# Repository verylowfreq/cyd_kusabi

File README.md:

# CyberDeck — ESP32-S3 SSH 端末

ESP32-S3 で作る、日本語入力可能な SSH 端末です。USB キーボードで打ち、480x320 の SPI 液晶に VT 互換のターミナルを出します。Wi-Fi で SSH に入り、PC を開かずに作業できます。

想定している使い方:

- 手元の簡易な SSH 端末として
- SSH 先で動く AI エージェント（Claude Code / Codex CLI など）に指示を出す端末として
- マイコンならではの GPIO・I2C・UART を直接触れる端末として
- 日本語のテキストを書く道具として
- WebAssemblyでユーザーアプリを書いて、スタンドアロンの制御端末として

**A SSH terminal built on the ESP32-S3.** It connects to Wi-Fi, takes
input from a USB keyboard, and shows an 80x26 VT terminal on a
480x320 SPI LCD. You can log in to a remote host over SSH (PTY, public-key or
password auth) and copy files with `scp`, all without a PC. It also has
built-in SKK Japanese input, a text editor, a small shell with GPIO / I2C /
ADC / UART commands, microSD storage, and user apps written in WebAssembly
(C or Rust SDK). Firmware is ESP-IDF v5.5 in C11, and the KiCad data for the
motherboard is included. Documentation is mainly in Japanese.

## できること

- **SSH**（libssh2）: PTY 付きで `top` や全画面アプリが動く。公開鍵認証（実機で鍵を作る）と
  パスワード認証、`known_hosts` によるホスト鍵の確認、切れたときの自動再接続
- **`scp`**: この機械だけでファイルを送る・取る（Linux / Windows の OpenSSH 相手で確認）
- **ターミナル**: UTF-8・全角幅・SGR 色・スクロール領域など VT100/xterm の主要部分。
  スクロールバック 200 行
- **SKK 日本語入力**: SKK-JISYO.L（約 17.5 万語）をフラッシュに載せ、学習結果も残す
- **テキストエディタ**: `edit <file>` で microSD 上のファイルを日本語入力つきで編集
- **シェル**: 行編集つき。ファイル操作、`wget`（HTTP / HTTPS）、シリアル端末 `uart`、
  `gpio` / `adc` / `i2c` など
- **WebAssembly アプリ**: `wasm run` で microSD 上の `.wasm` を実行。
  ファームを焼き直さずに機能を足せる。SDK は C と Rust
  （コンソール・ファイル・GPIO・ADC・I2C・UART・TCP/UDP・TLS）
- **ステータス帯**: `set statusbar on`（再起動後）で、Wi-Fi・SSH・かな入力・SD・電池電圧などを
  画面下に出す（既定は出さない。出すと本文は 80 x 25）

使い方の詳細は [取扱説明書 (docs/MANUAL.md)](docs/MANUAL.md) にあります。

## ハードウェア

| | |
|---|---|
| MCU | ESP32-S3-WROOM-1-N16R8（16MB flash / 8MB octal PSRAM）。Freenove ESP32-S3 開発ボードをマザーボードに載せる |
| 表示 | 480x320 SPI 液晶（ILI9488）。東雲フォント 12px で 80 桁 x 26 行（2 倍表示で 40 x 13） |
| 入力 | USB キーボード（ESP32-S3 の USB-OTG をホストとして使用） |
| 記憶 | microSD |
| 外部端子 | D-sub 9 ピン（RS-232C）、Grove（GPIO / I2C / UART） |
| 電源 | 単3形 NiMH 電池 x2（本体では充電しない） |

マザーボードの KiCad データ（回路図・基板・プロジェクト内ライブラリ・JLCPCB 用ガーバー）は
[hardware/cdk_motherboard/](hardware/cdk_motherboard/) にあります。
ピン割り当てや設計判断は [HARDWARE_DESIGN.md](HARDWARE_DESIGN.md) を参照してください。

> **基板 v1 には既知の誤りがあります。** microSD の SPI 4 本（GPIO39〜42）は、回路図・基板データ上の
> 信号名が実物と違います。ファームウェアのピン指定（`cdk_board.h`）が正しい方です。
> 詳しくは [HARDWARE_DESIGN.md の「基板 v1 の既知の誤り」](HARDWARE_DESIGN.md#基板-v1-の既知の誤り) を見てください。

ファームウェアは試作機として使った **M5Stack CoreS3** 向けにもビルドできます
（`--board cores3`）。

## リポジトリの構成

```
cyberdeck_firmware/      ファームウェア（ESP-IDF プロジェクト）
  components/              ESP-IDF に依存しない純 C のコア（PC 上でもビルド・テストする）
  components_port/         ESP-IDF に依存する部分（表示・USB・SD・Wi-Fi・SSH など）
  main/                    起動とコマンド
  host/                    PC 上で回す単体テスト（ctest）
  tools/                   cdk.py（ビルド・書き込み・画面取得など）、フォント・辞書の変換
  wasm-sdk/                WebAssembly アプリの SDK（C / Rust）
  wasm-apps/               サンプルアプリ
  DESIGN.md                ファームウェアの設計書
hardware/cdk_motherboard/  マザーボードの KiCad データ
docs/MANUAL.md             取扱説明書
images/                    この README の写真と回路図
LICENSE                    MIT License
HARDWARE_DESIGN.md         ハードウェア仕様と検証の記録
ABOUT.md                   最初の企画（開発開始時の要求）
DEV_STATS.md               開発の統計
```

## ビルド

必要なもの:

- [ESP-IDF v5.5.5](https://docs.espressif.com/projects/esp-idf/en/v5.5.5/)
- PC 側のテストには clang、CMake、Ninja、Python 3
- `tools/cdk.py` は pyserial の入った Python で動かす（`export.ps1` の後の `python` でよい）
- `tools/gen_secrets.py` は git を使う（生成物が gitignore されているかを確かめるため）
- 開発は Windows（PowerShell）で行っています

### 1. 初回だけ: `secrets.h` を作る

ファームは `main/secrets.h` を読みます。これは Wi-Fi・SSH の初期値を入れるためのファイルで、
リポジトリには入っていません。リポジトリ直下に `.env` を作り、
`tools/gen_secrets.py` で生成してください。値は空のままでもかまいません
（起動後に `set wifi.ssid ...` などで設定でき、NVS に保存されます）。

```
TEST_WIFI_SSID=
TEST_WIFI_PSK=
TEST_SSHSERVER_HOST=
TEST_SSHSERVER_USERNAME=
TEST_SSHSERVER_PASSWORD=
```

```powershell
cd cyberdeck_firmware
python tools\gen_secrets.py
```

`.env` と `secrets.h` は gitignore 済みです。値をコミットしないでください。

### 2. ビルドと書き込み

```powershell
. <ESP-IDF のパス>\export.ps1
python tools\cdk.py build --board v1    # v1 = このリポジトリの基板。CoreS3 なら cores3
python tools\cdk.py flash
python tools\cdk.py selftest            # 起動 → 画面を取得して PC 側の基準画像と比較
```

`selftest` は PC 側で基準画像を描いて比べるので、先に下の「PC 上のテスト」で `build-host` を作っておいてください。
`--board` は最初の 1 回だけ付ければ、次からは省いても前回の基板を引き継ぎます。

v1 は書き込み・ログ用と制御用の 2 本のシリアルを使います。COM ポートの既定は開発機のもの
（v1: 書き込み・ログ COM76 / 制御 COM75）なので、違う場合は
`python tools\cdk.py --prog COM5 --log COM5 --ctrl COM6 flash` のようにサブコマンドの**前**に書くか、
環境変数 `CDK_PROG` / `CDK_LOG` / `CDK_CTRL` で指定します。
詳しくは [取扱説明書の 12 章](docs/MANUAL.md#12-ファームウェアを更新する) と
[cyberdeck_firmware/README.md](cyberdeck_firmware/README.md) を参照してください。

### SKK 辞書

辞書はリポジトリに含めていません。SKK-JISYO.L を取ってきて、別パーティションに書き込みます。

```powershell
curl -O https://skk-dev.github.io/dict/SKK-JISYO.L.unannotated.gz
# 展開してから
python tools\cdk.py dict SKK-JISYO.L.unannotated
```

### PC 上のテスト（実機不要）

```powershell
cd cyberdeck_firmware
cmake -S host -B build-host -G Ninja -DCMAKE_C_COMPILER=clang
cmake --build build-host
ctest --test-dir build-host --output-on-failure
```

VT パーサ、文字幅、フォント描画、SKK、シェル、WebAssembly の実行系などは
`components/` の純 C コードで、PC 上で検証できます。

## 開発について

このファームウェアは、AI エージェント（Claude Code）が実機でのビルド・書き込み・
画面の取得まで自分で回しながら開発しました。人間は方針の判断、配線や目視の確認などを
担当しています。その経過の数字（ビルド回数、不具合の数と見つけ方、人間が介入した回数など）を
[DEV_STATS.md](DEV_STATS.md) にまとめています。

設計の判断とその理由は [cyberdeck_firmware/DESIGN.md](cyberdeck_firmware/DESIGN.md) に残しています。

## ライセンス

[MIT License](LICENSE) © 2026 Mitsumine Suzu (verylowfreq)

同梱しているサードパーティのコードとデータは、それぞれのライセンスに従います。

| もの | 場所 | ライセンス |
|---|---|---|
| libssh2 1.11.1 | `cyberdeck_firmware/components_port/libssh2/upstream/` | BSD-3-Clause（`COPYING`） |
| wasm3（commit 2b4a5fa） | `cyberdeck_firmware/components_port/wasm3/upstream/` | MIT（`LICENSE`） |
| 東雲フォント（変換済みデータ） | `cyberdeck_firmware/components/cdk_font/shinonome12.cdkfont` | Public Domain |

ESP-IDF のコンポーネント（`esp_lcd_ili9488` など）はビルド時に取得され、リポジトリには含まれません。
SKK 辞書も含めていません。

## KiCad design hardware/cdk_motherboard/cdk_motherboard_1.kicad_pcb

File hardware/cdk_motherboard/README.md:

# cdk_motherboard（基板 v1）

CyberDeck のマザーボードの KiCad データ。Freenove ESP32-S3 開発ボードと
480x320 の SPI 液晶モジュール（microSD スロット付き）を載せる。

| ファイル | 中身 |
|---|---|
| `cdk_motherboard_1.kicad_pro` / `.kicad_sch` / `.kicad_pcb` | プロジェクト・回路図・基板 |
| `ProjectLibrary.kicad_sym` / `ProjectLibrary.pretty/` | このプロジェクトで使うシンボルとフットプリント |
| `jlcpcb/gerber/` / `jlcpcb/production_files/` | JLCPCB に出したガーバー |

## 既知の誤り

**microSD の SPI 4 本（GPIO39〜42）は、回路図・基板データの信号名が実物と違う。**
液晶モジュールの SD のパッドの並びが、フットプリントでは逆順になっている。
基板はそのまま使えて、ファームウェアのピン指定（`cdk_board.h`）が実物に合わせてある。

ほかに、**部品の名前が実物と違う**ところが 2 つある（配線は正しい）。

- RS-232C の IC（U3）: シンボルは `ADM232A`。実装は 3.3V 対応の **XD3232**
- 外部端子（CN2〜CN4）: フットプリントは JST PH。実装は **Grove**

詳細（SD の実物の対応表、プルアップ抵抗のずれ）は
[HARDWARE_DESIGN.md の「基板 v1 の既知の誤り」](../../HARDWARE_DESIGN.md#基板-v1-の既知の誤り)。
仕様の検討から変わったところ（電源・RS-232C の IC など）も同じ文書の「基板 v1」にある。

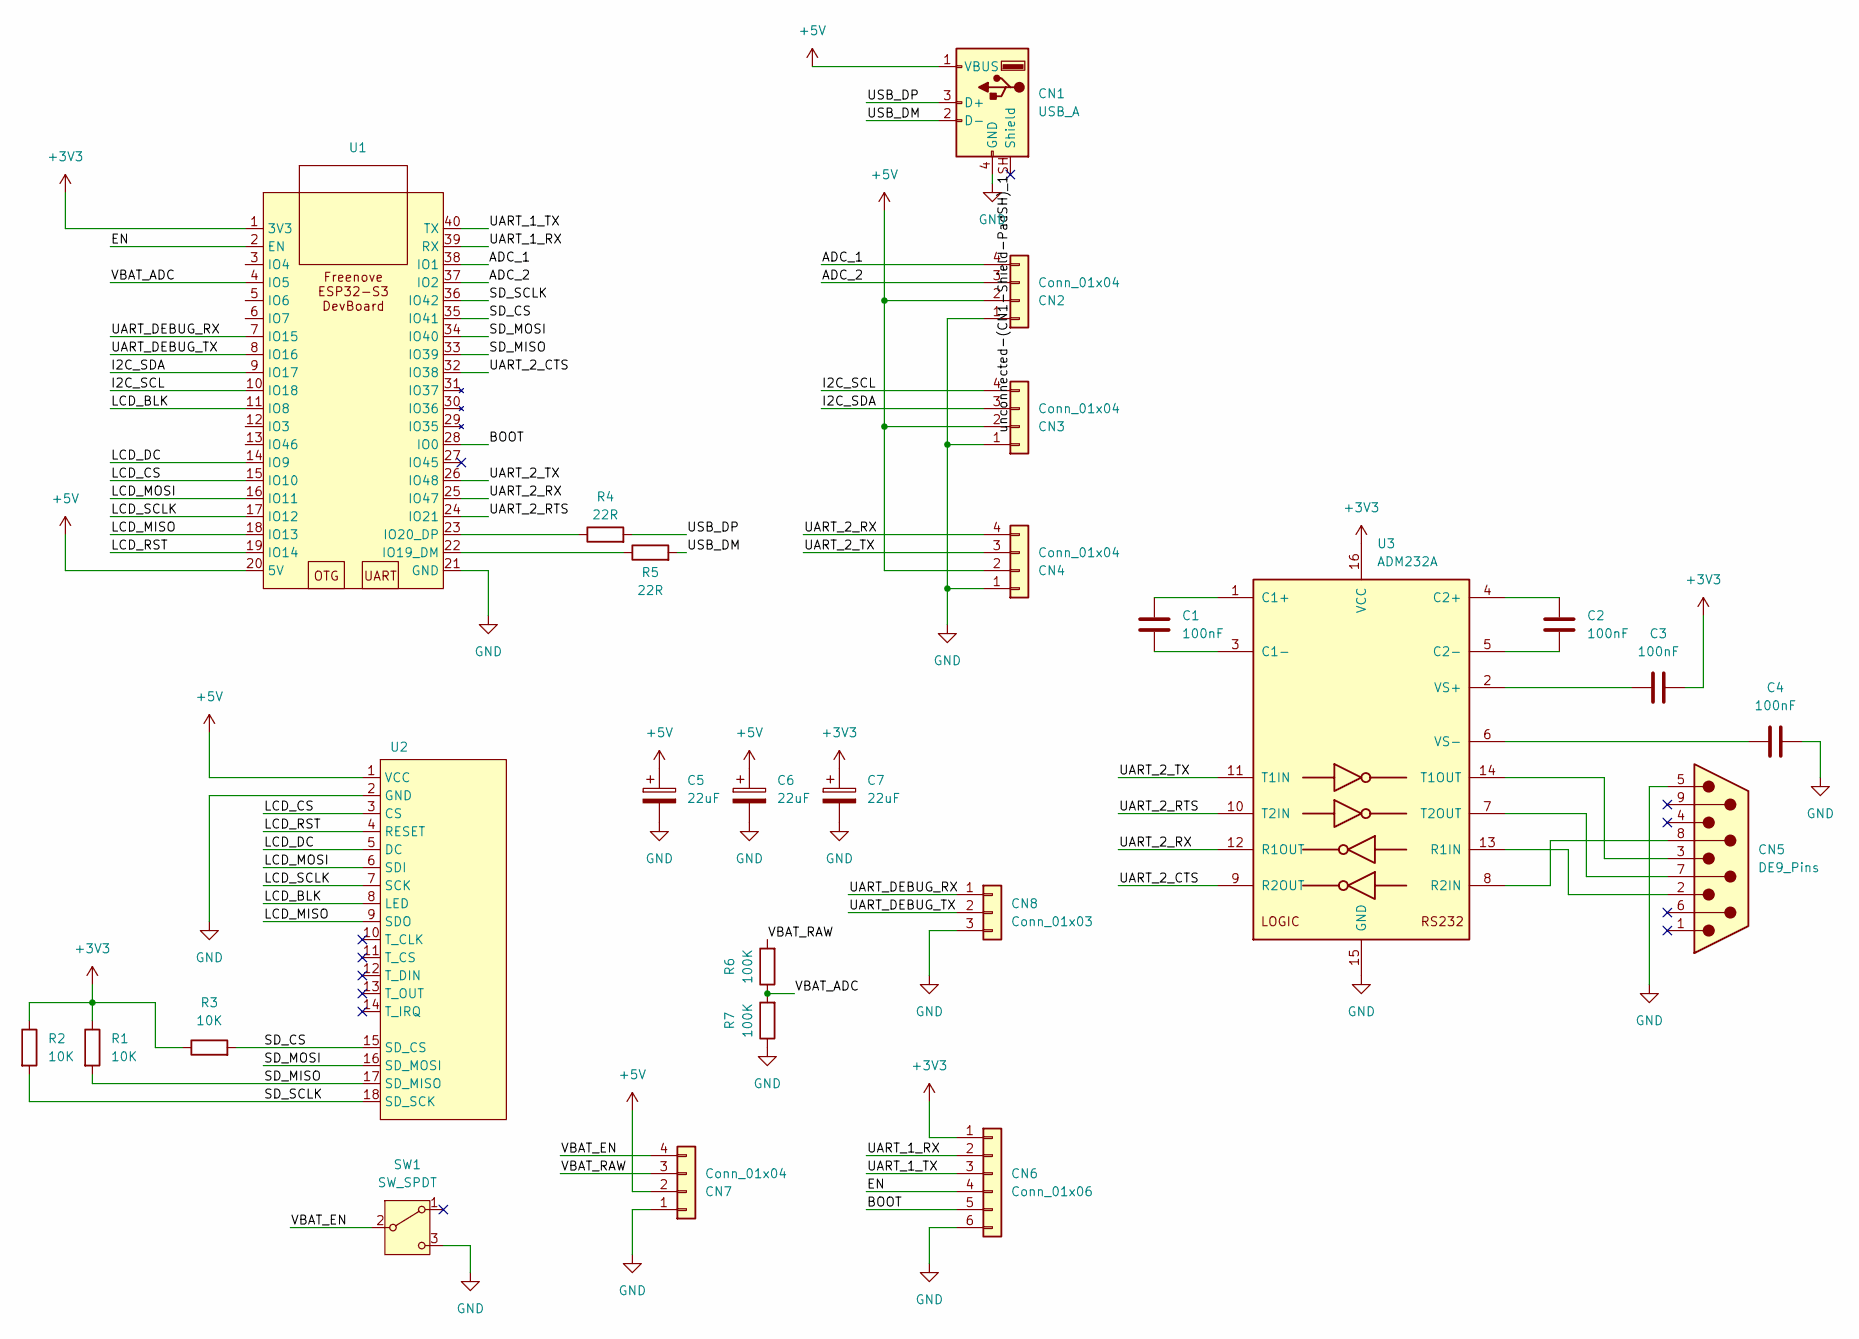
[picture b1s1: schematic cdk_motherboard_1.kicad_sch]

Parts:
C1, C2, C3, C4: 100nF; C_Disc_D3.0mm_W1.6mm_P2.50mm
C5, C6, C7: 22uF; CP_Radial_D5.0mm_P2.00mm
CN1: USB_A; USB Type-A Receptacle 5075AR-04-WH
CN2, CN3, CN4, CN7: Conn_01x04; JST_PH_B4B-PH-K_1x04_P2.00mm_Vertical
CN5: DE9_Pins; D-Sub 9pin Plug DMR-09PGG
CN6: Conn_01x06; PinSocket_1x06_P2.54mm_Vertical
CN8: Conn_01x03; PinSocket_1x03_P2.54mm_Vertical
R1, R2, R3: 10K; R_Axial_DIN0207_L6.3mm_D2.5mm_P7.62mm_Horizontal
R4, R5: 22R; R_Axial_DIN0207_L6.3mm_D2.5mm_P7.62mm_Horizontal
R6, R7: 100K; R_Axial_DIN0207_L6.3mm_D2.5mm_P7.62mm_Horizontal
SW1: SW_SPDT; Toggle Switch 2MS1-T1-B4-VS2-Q-E-S
U1: Freenove ESP32-S3 DevBoard
U2: LCD_480x320_4inch_SD
U3: ADM232A; DIP-16_W7.62mm

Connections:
+3V3: C3.2, C7.1, CN6.1, R1.1, R2.1, R3.1, U1.1 (3V3), U3.16 (VCC)
+5V: C5.1, C6.1, CN1.1 (VBUS), CN2.2, CN3.2, CN4.2, CN7.2, U1.20 (5V), U2.1 (VCC)
/ADC_1: CN2.4, U1.38 (IO1)
/ADC_2: CN2.3, U1.37 (IO2)
/BOOT: CN6.5, U1.28 (IO0)
/EN: CN6.4, U1.2 (EN)
/I2C_SCL: CN3.4, U1.10 (IO18)
/I2C_SDA: CN3.3, U1.9 (IO17)
/LCD_BLK: U1.11 (IO8), U2.8 (LED)
/LCD_CS: U1.15 (IO10), U2.3 (CS)
/LCD_DC: U1.14 (IO9), U2.5 (DC)
/LCD_MISO: U1.18 (IO13), U2.9 (SDO)
/LCD_MOSI: U1.16 (IO11), U2.6 (SDI)
/LCD_RST: U1.19 (IO14), U2.4 (RESET)
/LCD_SCLK: U1.17 (IO12), U2.7 (SCK)
/SD_CS: R3.2, U1.35 (IO41), U2.15 (SD_CS)
/SD_MISO: R1.2, U1.33 (IO39), U2.17 (SD_MISO)
/SD_MOSI: U1.34 (IO40), U2.16 (SD_MOSI)
/SD_SCLK: R2.2, U1.36 (IO42), U2.18 (SD_SCK)
/UART_1_RX: CN6.2, U1.39 (RX)
/UART_1_TX: CN6.3, U1.40 (TX)
/UART_2_CTS: U1.32 (IO38), U3.9 (R2OUT)
/UART_2_RTS: U1.24 (IO21), U3.10 (T2IN)
/UART_2_RX: CN4.4, U1.25 (IO47), U3.12 (R1OUT)
/UART_2_TX: CN4.3, U1.26 (IO48), U3.11 (T1IN)
/UART_DEBUG_RX: CN8.1, U1.7 (IO15)
/UART_DEBUG_TX: CN8.2, U1.8 (IO16)
/USB_DM: CN1.2 (D-), R5.2
/USB_DP: CN1.3 (D+), R4.2
/VBAT_ADC: R6.1, R7.2, U1.4 (IO5)
/VBAT_EN: CN7.4, SW1.2 (B)
/VBAT_RAW: CN7.3, R6.2
/unconnected-(CN1-Shield-PadSH)_1: CN1.SH (Shield)
/unconnected-(CN1-Shield-PadSH)_1_1: CN1.SH (Shield)
GND: C4.2, C5.2, C6.2, C7.2, CN1.4 (GND), CN2.1, CN3.1, CN4.1, CN5.5, CN6.6, CN7.1, CN8.3, R7.1, SW1.3 (C), U1.21 (GND), U2.2 (GND), U3.15 (GND)
unnamed: R5.1, U1.22 (IO19_DM)
unnamed: R4.1, U1.23 (IO20_DP)
unnamed: C1.1, U3.1 (C1+)
unnamed: C1.2, U3.3 (C1-)
unnamed: C2.1, U3.4 (C2+)
unnamed: C2.2, U3.5 (C2-)
unnamed: CN5.2, U3.13 (R1IN)
unnamed: CN5.8, U3.8 (R2IN)
unnamed: CN5.3, U3.14 (T1OUT)
unnamed: CN5.7, U3.7 (T2OUT)
unnamed: C3.1, U3.2 (VS+)
unnamed: C4.1, U3.6 (VS-)

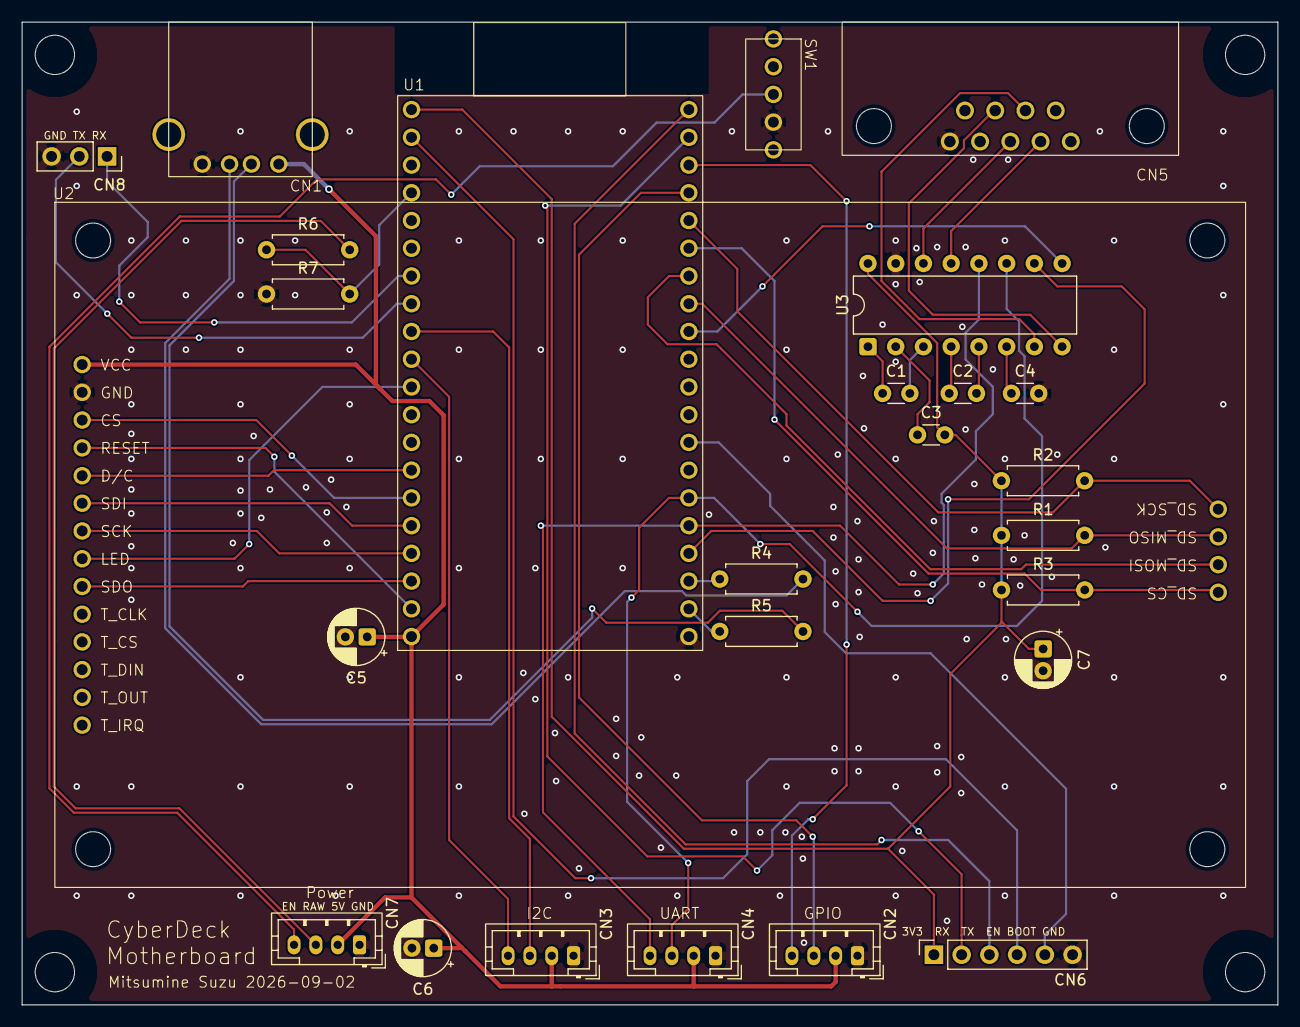
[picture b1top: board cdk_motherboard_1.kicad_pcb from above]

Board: 2 copper layers, 115.0 x 90.0 mm, 26 parts (0 on the bottom side), 45 nets.
